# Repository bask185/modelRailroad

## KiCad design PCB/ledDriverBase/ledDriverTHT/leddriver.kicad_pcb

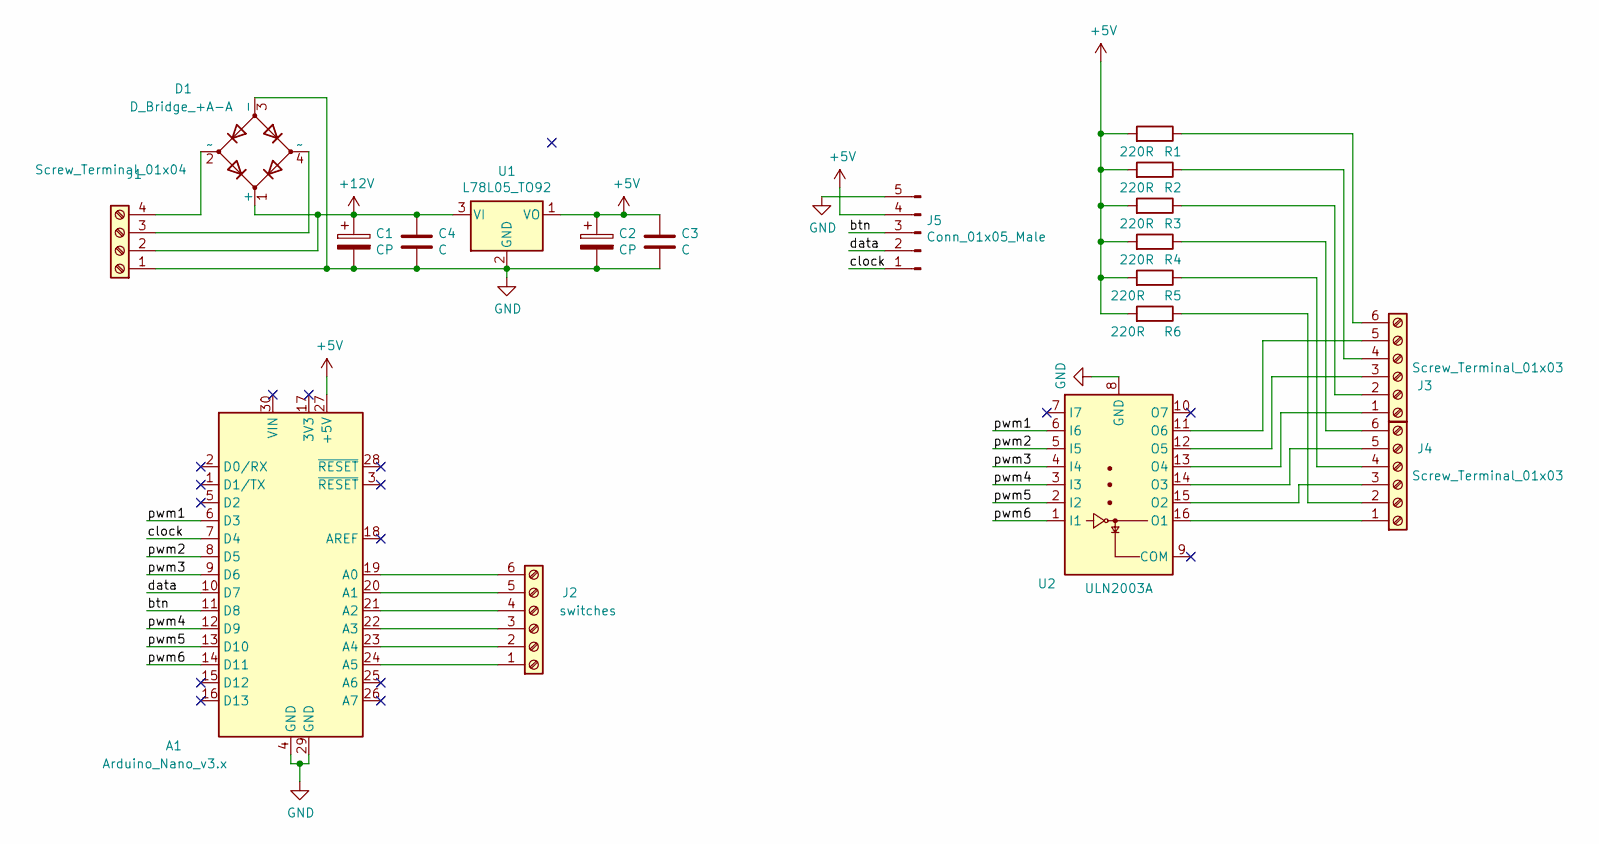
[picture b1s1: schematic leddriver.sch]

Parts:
A1: Arduino_Nano_v3.x; Arduino_Nano
C1, C2: CP; CP_Radial_D4.0mm_P1.50mm
C3, C4: C; C_Disc_D3.0mm_W1.6mm_P2.50mm
D1: D_Bridge_+A-A; Diode_Bridge_Round_D9.0mm
J1: Screw_Terminal_01x04; TerminalBlock_bornier-4_P5.08mm
J2: switches; TerminalBlock_bornier-6_P5.08mm
J3, J4: Screw_Terminal_01x03; TerminalBlock_bornier-6_P5.08mm
J5: Conn_01x05_Male; PinHeader_1x05_P2.54mm_Vertical
R1, R2, R3, R4, R5, R6: 220R; R_Axial_DIN0204_L3.6mm_D1.6mm_P7.62mm_Horizontal
U1: L78L05_TO92; TO-92_Inline
U2: ULN2003A; DIP-16_W7.62mm

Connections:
+5V: A1.27 (+5V), C2.1, C3.1, J5.4, R1.2, R2.2, R3.2, R4.2, R5.2, R6.2, U1.1 (VO)
+12V: C1.1, C4.1, D1.1 (+), J1.2, U1.3 (VI)
/btn: A1.11 (D8), J5.3
/clock: A1.7 (D4), J5.1
/data: A1.10 (D7), J5.2
/pwm1: A1.6 (D3), U2.6 (I6)
/pwm2: A1.8 (D5), U2.5 (I5)
/pwm3: A1.9 (D6), U2.4 (I4)
/pwm4: A1.12 (D9), U2.3 (I3)
/pwm5: A1.13 (D10), U2.2 (I2)
/pwm6: A1.14 (D11), U2.1 (I1)
GND: A1.4 (GND), A1.29 (GND), C1.2, C2.2, C3.2, C4.2, D1.3 (-), J1.1, J5.5, U1.2 (GND), U2.8 (GND)
unnamed: A1.19 (A0), J2.6
unnamed: A1.20 (A1), J2.5
unnamed: A1.21 (A2), J2.4
unnamed: A1.22 (A3), J2.3
unnamed: A1.23 (A4), J2.2
unnamed: A1.24 (A5), J2.1
unnamed: D1.2 (~~), J1.4
unnamed: D1.4 (~~), J1.3
unnamed: J3.1, U2.13 (O4)
unnamed: J3.2, R3.1
unnamed: J3.3, U2.12 (O5)
unnamed: J3.4, R2.1
unnamed: J3.5, U2.11 (O6)
unnamed: J3.6, R1.1
unnamed: J4.1, U2.16 (O1)
unnamed: J4.2, R6.1
unnamed: J4.3, U2.15 (O2)
unnamed: J4.4, R5.1
unnamed: J4.5, U2.14 (O3)
unnamed: J4.6, R4.1

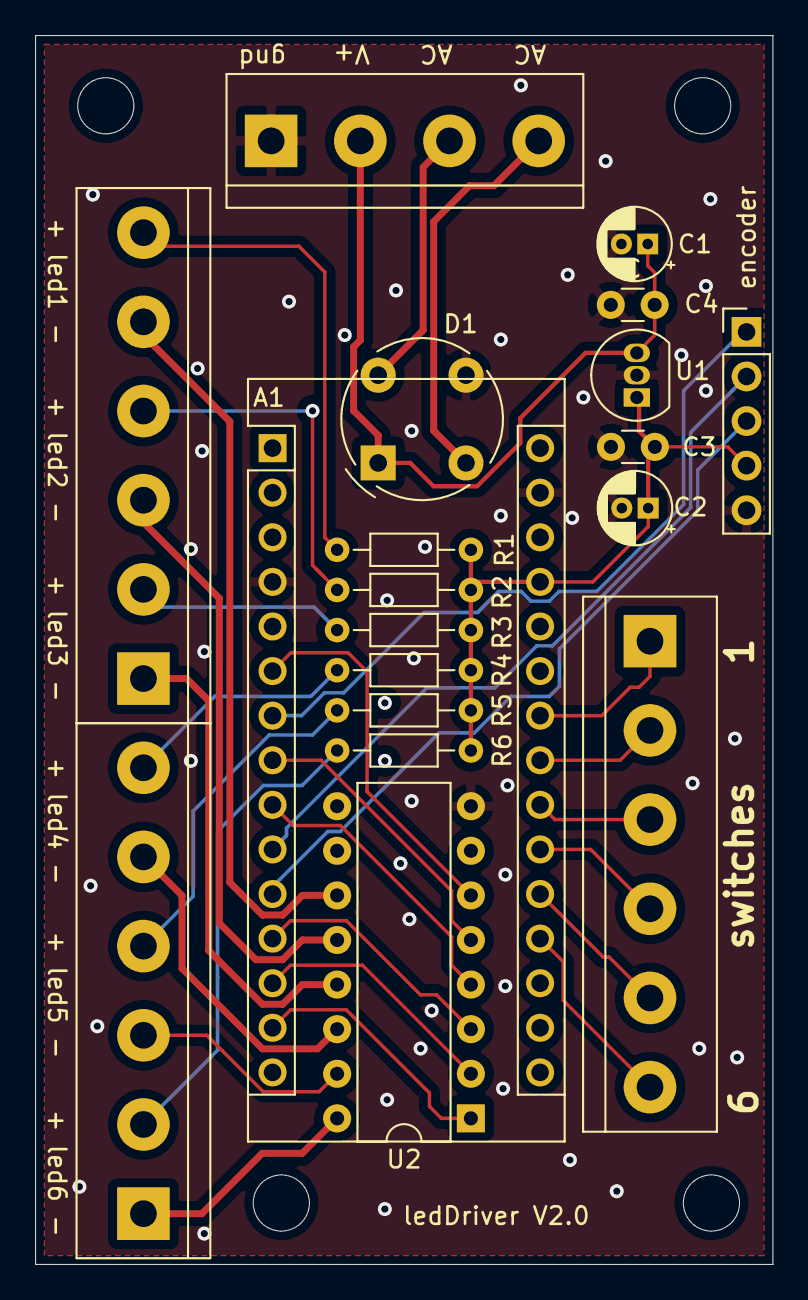
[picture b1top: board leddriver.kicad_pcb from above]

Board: 2 copper layers, 42.0 x 70.0 mm, 19 parts (0 on the bottom side), 32 nets.
